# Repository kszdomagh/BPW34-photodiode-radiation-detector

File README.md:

# BPW34-photodiode-radiation-detector

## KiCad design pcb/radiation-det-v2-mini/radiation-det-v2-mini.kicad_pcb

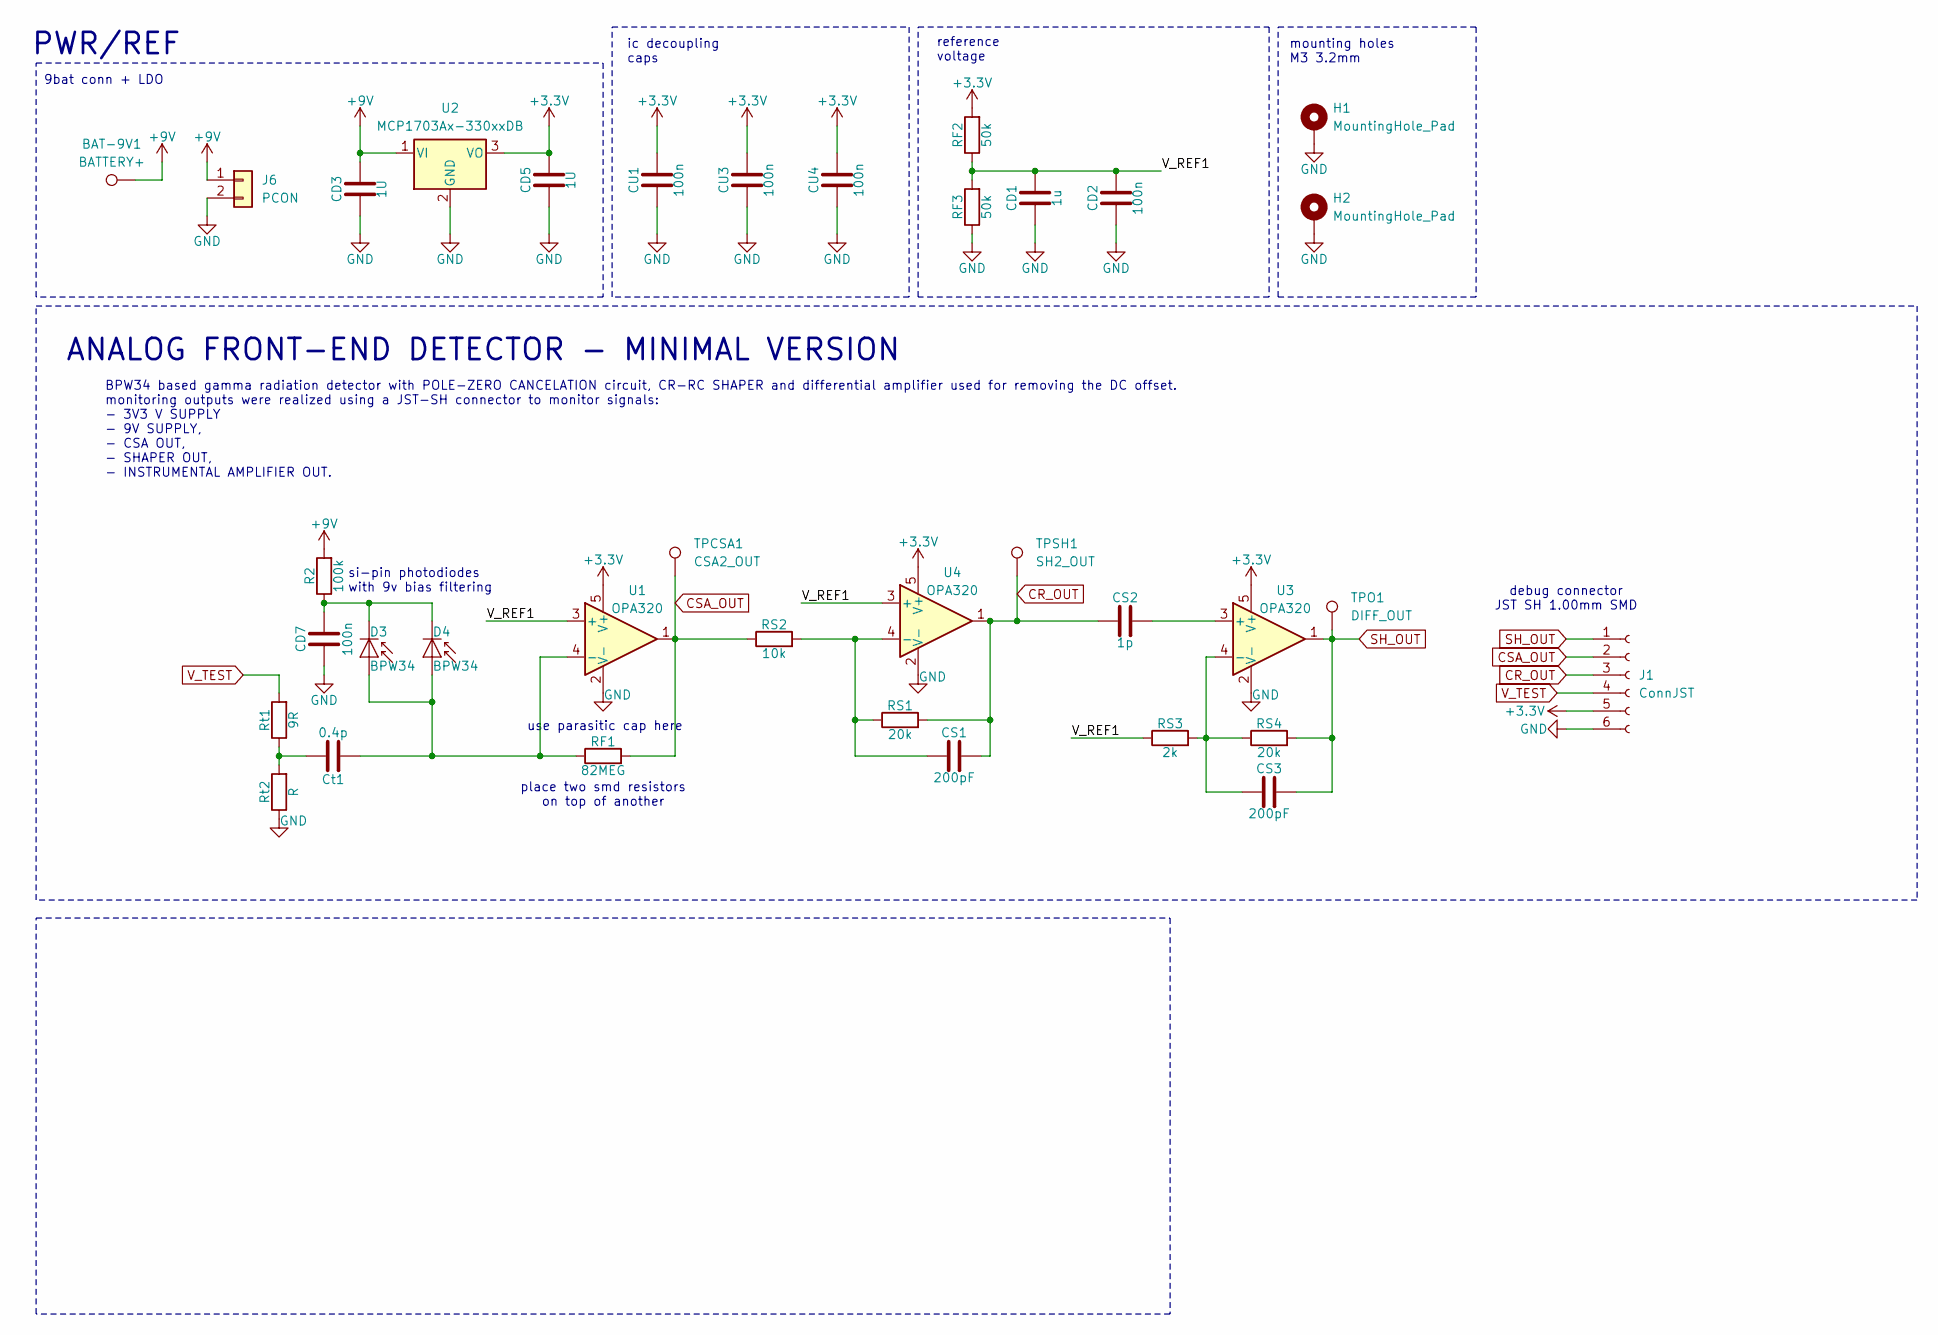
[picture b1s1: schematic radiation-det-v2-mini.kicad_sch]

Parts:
BAT-9V1: BATTERY+; TestPoint_Pad_1.0x1.0mm
CD1: 1u; C_0805_2012Metric
CD2, CD7: 100n; C_0805_2012Metric
CD3, CD5: 1U; C_0805_2012Metric
CS1, CS3: 200pF; C_0805_2012Metric
CS2: 1p; C_0805_2012Metric
CU1, CU3, CU4: 100n; C_0805_2012Metric
Ct1: 0.4p; C_0805_2012Metric
D3, D4: BPW34; Osram_DIL2_4.3x4.65mm_P5.08mm
H1, H2: MountingHole_Pad; MountingHole_3.2mm_M3_DIN965_Pad
J1: ConnJST; JST_SH_BM06B-SRSS-TB_1x06-1MP_P1.00mm_Vertical
J6: PCON; PinHeader_1x02_P2.54mm_Vertical
R2: 100k; R_0805_2012Metric
RF1: 82MEG; R_0805_2012Metric
RF2, RF3: 50k; R_0805_2012Metric
RS1, RS4: 20k; R_0805_2012Metric
RS2: 10k; R_0805_2012Metric
RS3: 2k; R_0805_2012Metric
Rt1: 9R; R_0805_2012Metric
Rt2: R; R_0805_2012Metric
TPCSA1: CSA2_OUT; TestPoint_Pad_D1.5mm
TPO1: DIFF_OUT; TestPoint_Pad_D1.5mm
TPSH1: SH2_OUT; TestPoint_Pad_D1.5mm
U1, U3, U4: OPA320; SOT-23-5
U2: MCP1703Ax-330xxDB; SOT-223-3_TabPin2

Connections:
+3.3V: CD5.2, CU1.2, CU3.2, CU4.2, J1.5, RF2.2, U1.5 (V+), U2.3 (VO), U3.5 (V+), U4.5 (V+)
+9V: BAT-9V1.1, CD3.2, J6.1, R2.2, U2.1 (VI)
/V_REF1: CD1.2, CD2.2, RF2.1, RF3.2, RS3.1, U1.3 (+), U4.3 (+)
CR_OUT: CS1.2, CS2.1, J1.3, RS1.2, TPSH1.1, U4.1
CSA_OUT: J1.2, RF1.2, RS2.1, TPCSA1.1, U1.1
GND: CD1.1, CD2.1, CD3.1, CD5.1, CD7.1, CU1.1, CU3.1, CU4.1, H1.1, H2.1, J1.6, J6.2, RF3.1, Rt2.1, U1.2 (V-), U2.2 (GND), U3.2 (V-), U4.2 (V-)
unnamed: Ct1.2, Rt1.1, Rt2.2
unnamed: Ct1.1, D3.2 (A), D4.2 (A), RF1.1, U1.4 (-)
unnamed: CD7.2, D3.1 (K), D4.1 (K), R2.1
unnamed: CS2.2, U3.3 (+)
unnamed: CS3.1, RS3.2, RS4.1, U3.4 (-)
unnamed: CS1.1, RS1.1, RS2.2, U4.4 (-)
SH_OUT: CS3.2, J1.1, RS4.2, TPO1.1, U3.1
V_TEST: J1.4, Rt1.2

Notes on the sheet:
si-pin photodiodes with 9v bias filtering
BPW34 based gamma radiation detector with POLE-ZERO CANCELATION circuit, CR-RC SHAPER and differential amplifier used for removing the DC offset. monitoring outputs were realized using a JST-SH connector to monitor signals: - 3V3 V SUPPLY - 9V SUPPLY, - CSA OUT, - SHAPER OUT, - INSTRUMENTAL AMPLIFI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
place two smd resistors on top of another
9bat conn + LDO
ANALOG FRONT-END DETECTOR - MINIMAL VERSION
reference voltage
PWR/REF
mounting holes M3 3.2mm
ic decoupling caps
debug connector JST SH 1.00mm SMD
use parasitic cap here

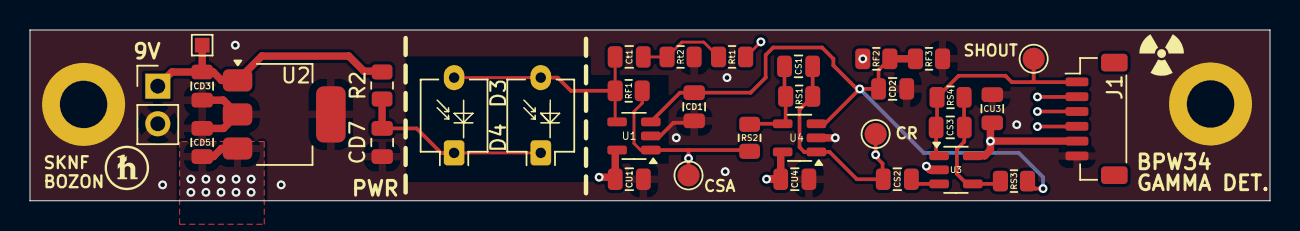
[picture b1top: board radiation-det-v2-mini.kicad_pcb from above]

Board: 4 copper layers, 83.7 x 11.5 mm, 36 parts (0 on the bottom side), 14 nets.

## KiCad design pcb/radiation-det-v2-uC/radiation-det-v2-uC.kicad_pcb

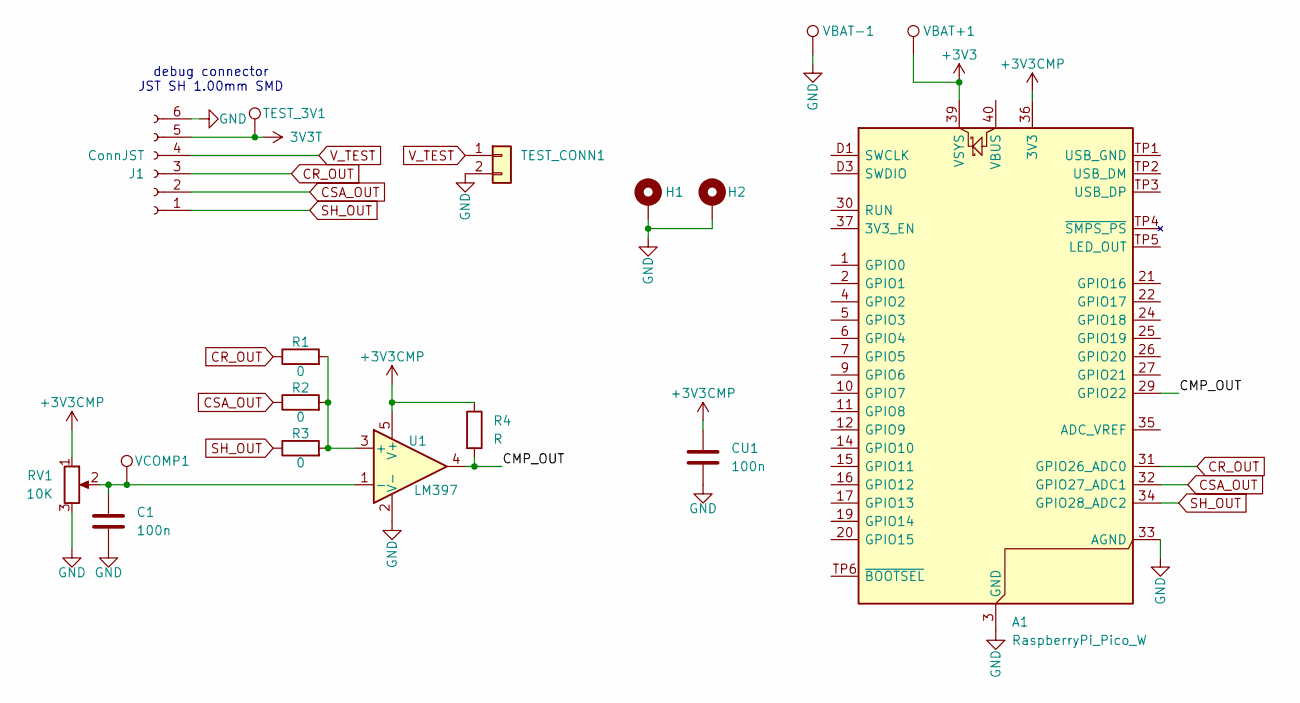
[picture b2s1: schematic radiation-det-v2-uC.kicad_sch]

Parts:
A1: RaspberryPi_Pico_W; RaspberryPi_Pico_W_SMD
C1: 100n; C_0805_2012Metric
CU1: 100n; C_0805_2012Metric
H1, H2: MountingHole_Pad; MountingHole_3.2mm_M3_DIN965_Pad
J1: ConnJST; JST_SH_BM06B-SRSS-TB_1x06-1MP_P1.00mm_Vertical
R1, R2, R3: 0; R_0805_2012Metric
R4: R; R_0805_2012Metric
RV1: 10K; Potentiometer_Bourns_3214G_Horizontal
TEST_3V1: TestPoint; TestPoint_Pad_1.5x1.5mm
TEST_CONN1: Conn_01x02; PinHeader_1x02_P2.54mm_Vertical
U1: LM397; SOT-23-5
VBAT+1: TestPoint; TestPoint_Pad_1.5x1.5mm
VBAT-1: TestPoint; TestPoint_Pad_1.5x1.5mm
VCOMP1: TestPoint; TestPoint_Pad_1.5x1.5mm

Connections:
3V3T: J1.5, TEST_3V1.1
+3V3: A1.39 (VSYS), VBAT+1.1
+3V3CMP: A1.36 (3V3), CU1.1, R4.1, RV1.1, U1.5 (V+)
/CMP_OUT: A1.29 (GPIO22), R4.2, U1.4
CR_OUT: A1.31 (GPIO26_ADC0), J1.3, R1.1
CSA_OUT: A1.32 (GPIO27_ADC1), J1.2, R2.1
GND: A1.3 (GND), A1.8 (GND), A1.13 (GND), A1.18 (GND), A1.23 (GND), A1.28 (GND), A1.33 (AGND), A1.38 (GND), A1.D2 (GND), C1.2, CU1.2, H1.1, H2.1, J1.6, RV1.3, TEST_CONN1.2, U1.2 (V-), VBAT-1.1
unnamed: R1.2, R2.2, R3.2, U1.3 (+)
unnamed: C1.1, RV1.2, U1.1 (-), VCOMP1.1
SH_OUT: A1.34 (GPIO28_ADC2), J1.1, R3.1
V_TEST: J1.4, TEST_CONN1.1

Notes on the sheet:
debug connector JST SH 1.00mm SMD

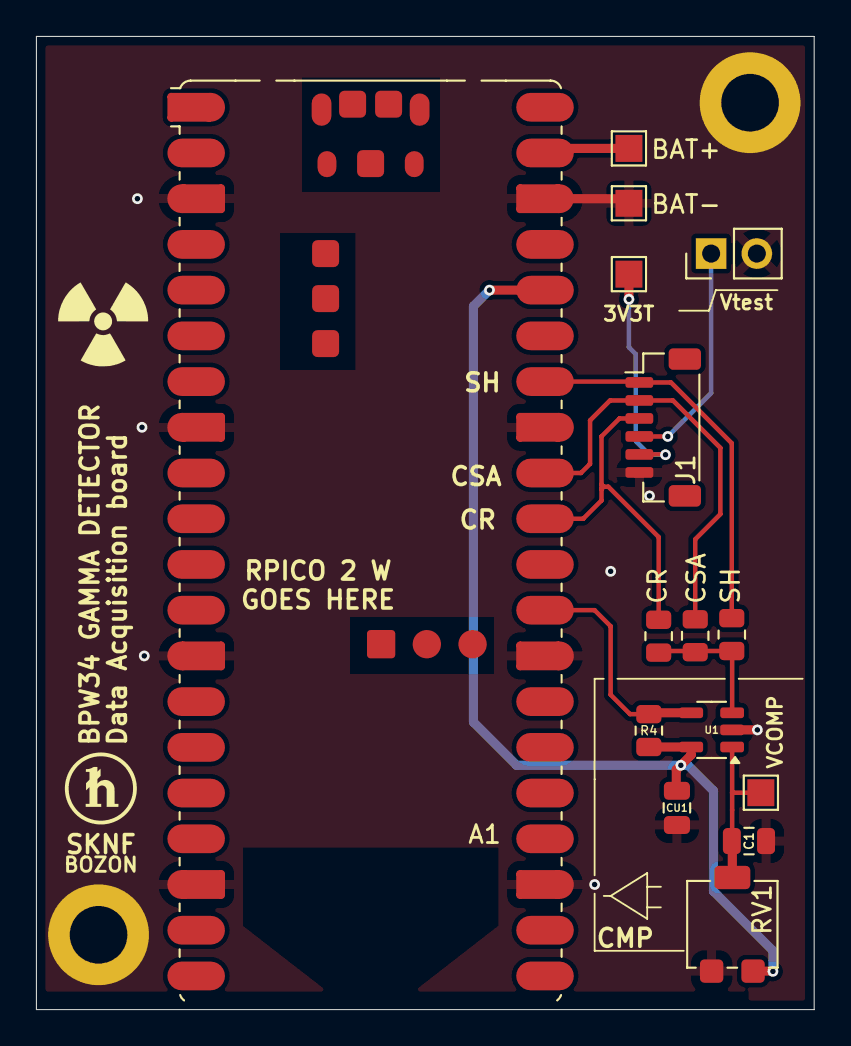
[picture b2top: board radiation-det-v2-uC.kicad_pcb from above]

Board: 2 copper layers, 43.2 x 54.1 mm, 17 parts (0 on the bottom side), 11 nets.
